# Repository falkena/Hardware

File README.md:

# Hardware
Some hardware extensions i developed for RaspberryPi.

Boards are made for rail - din enclosures.

Boards and schematics are published under Open Hardware License:
http://www.ohwr.org/licenses/cern-ohl/v1.2

DigitalIO
----------
MCP23017 based board supporting 8 digital inputs/outputs.
Inputs are opto-isolated and can be used up to 24V DC.
Outputs are relay driven. More details can be found in
documentation for used components.

Board can be driven for example with Pi4J.

AnalogI
-------
MCP3424 based board supporting 4 analog inputs.
Inputs are opto-isolated and can measure signals up to 10V DC.

Board can be driven for example with Pi4J.

Very special thanks to the guys from http://www.mikrocontroller.net

Automation board
----------------

Automation board for Raspberry PI. Designed to work with input voltage 15-24V.
Provides I2C connector, two wireless receiver for 433 and 868 MHZ as well PWM
fan 4 pin. Additional 2 pin connector can be used for shutdown with help of
`gpio-shutdown` overlay. Required 5V supply is done via MP1584 and MP2482 based
dc/dc step-down modules. See `modules` Eagle library for details.

Rain sensor
-----------

LM358 OpAmp based rain sensor detector. Designed to work with input voltage 15-24V.
Provides input and 10V digital outputs as well possibility to control heating.

Drop sensor is based on https://github.com/ranseyer/home-automatics/tree/master/Rain-Sensor/Kamm

Eagle
-------
Contains some cheap DIY boards i've used. Follow components are modeled now:
- RXB6 wireless receiver module
- RXB8 wireless receiver module
- CC1101 wireless transceiver/receiver module
- MP1584 based dc/dc step-down module
- MP2482 based dc/dc step-down module

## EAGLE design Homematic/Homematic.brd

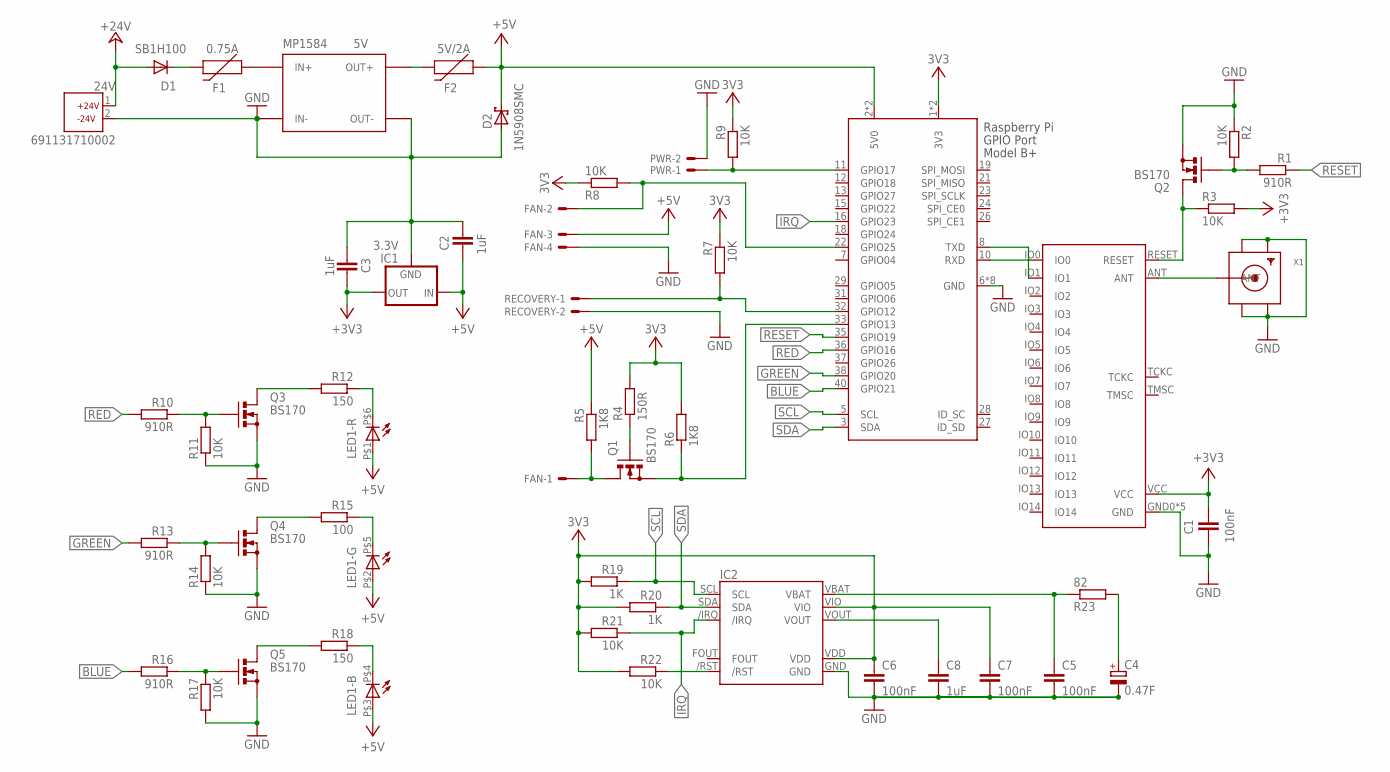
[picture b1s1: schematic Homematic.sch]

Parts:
24V: 691131710002
C1, C5, C6, C7: 100nF; C0805
C2, C3, C8: 1uF; C0805
C4: 0.47F; GOLDCAP-V
D1: SB1H100; DO41-7.6
D2: 1N5908SMC; SMC
F1: 0.75A; RGEF250
F2: 5V/2A; RGEF250
FAN: 22-23-2041
IC1: 3.3V; TO92
IC2: RX8130SMT; SMT-3225-10
LED1: LED-RGB; PLCC6
MP1584: 5V; MP1584V
PWR: 22-23-2021
Q1, Q2, Q3, Q4, Q5: BS170; SOT54E
R1: 910R; 0204/5
R2, R21, R22: 10K; 0204/5
R3, R7, R8, R9, R11, R14, R17: 10K; 0204V
R4: 150R; 0204V
R5, R6: 1K8; 0204V
R10, R13, R16: 910R; 0204V
R12, R18: 150; 0204V
R15: 100; 0204V
R19, R20: 1K; 0204/5
R23: 82; 0204/5
RECOVERY: 22-23-2021
RPI: RASPI_BOARD_B+#_F; RASPI_BOARD_B+_FULL
TRX2-TIF: TRXC2-TIFSMD; TRXC2-TIF
X1: SMACONNECTOR; SMA90_DIP

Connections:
3V3: C6.1, C7.1, IC2.VDD, IC2.VIO, R7.1, R8.1, R9.1, R19.2, R20.2, R21.2, R22.2, RPI.1 (3V3), RPI.17 (3V3)
+3V3: C1.1, C3.1, IC1.3 (OUT), R3.2, TRX2-TIF.VCC
+5V: C2.2, D2.C, F2.P$1 (1), FAN.3, IC1.2 (IN), LED1.P$1 (A), LED1.P$2 (A), LED1.P$3 (A), R5.1, RPI.2 (5V0), RPI.4 (5V0)
+24V: 24V.1, D1.A
BLUE: R16.2, RPI.40 (GPIO21)
GND: 24V.2, C1.2, C2.1, C3.2, C4.-, C5.2, C6.2, C7.2, C8.2, D2.A, FAN.4, IC1.1 (GND), IC2.GND, MP1584.IN-0 (IN-), MP1584.IN-1 (IN-), MP1584.OUT-0 (OUT-), MP1584.OUT-1 (OUT-), PWR.2, Q2.S, Q3.S, Q4.S, Q5.S, R2.1, R11.1, R14.1, R17.2, RECOVERY.2, RPI.6 (GND), RPI.9 (GND), RPI.14 (GND), RPI.20 (GND), RPI.25 (GND), RPI.30 (GND), RPI.34 (GND), RPI.39 (GND), TRX2-TIF.GND0 (GND), TRX2-TIF.GND1 (GND), TRX2-TIF.GND2 (GND), TRX2-TIF.GND3 (GND), TRX2-TIF.GND4 (GND), X1.GND1, X1.GND2, X1.GND3, X1.GND4
GREEN: R13.2, RPI.38 (GPIO20)
IRQ: IC2./IRQ, R21.1, RPI.16 (GPIO23)
unnamed: Q3.G, R10.1, R11.2
unnamed: RPI.10 (RXD), TRX2-TIF.IO0
unnamed: RPI.8 (TXD), TRX2-TIF.IO1
unnamed: F2.P$2 (2), MP1584.OUT+0 (OUT+), MP1584.OUT+1 (OUT+)
unnamed: Q4.G, R13.1, R14.2
unnamed: Q3.D, R12.2
unnamed: F1.P$1 (1), MP1584.IN+0 (IN+), MP1584.IN+1 (IN+)
unnamed: TRX2-TIF.ANT, X1.ANTENNA (ANT)
unnamed: D1.C, F1.P$2 (2)
unnamed: Q2.G, R1.2, R2.2
unnamed: Q1.G, R4.1
unnamed: Q5.G, R16.1, R17.1
unnamed: Q1.S, R6.1, RPI.33 (GPIO13)
unnamed: FAN.1, Q1.D, R5.2
unnamed: Q2.D, R3.1, TRX2-TIF.RESET
unnamed: Q4.D, R15.2
unnamed: Q5.D, R18.2
unnamed: LED1.P$6 (C), R12.1
unnamed: LED1.P$4 (C), R18.1
unnamed: LED1.P$5 (C), R15.1
unnamed: PWR.1, R9.2, RPI.11 (GPIO17)
unnamed: FAN.2, R8.2, RPI.22 (GPIO25)
unnamed: C4.+, R23.2
unnamed: C5.1, IC2.VBAT, R23.1
unnamed: IC2./RST, R22.1
unnamed: R7.2, RECOVERY.1, RPI.32 (GPIO12)
RED: R10.2, RPI.36 (GPIO16)
RESET: R1.1, RPI.35 (GPIO19)
SCL: IC2.SCL, R19.1, RPI.5 (SCL)
SDA: IC2.SDA, R20.1, RPI.3 (SDA)
V+: R4.2, R6.2
VOUT: C8.1, IC2.VOUT

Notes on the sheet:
+24V
-24V

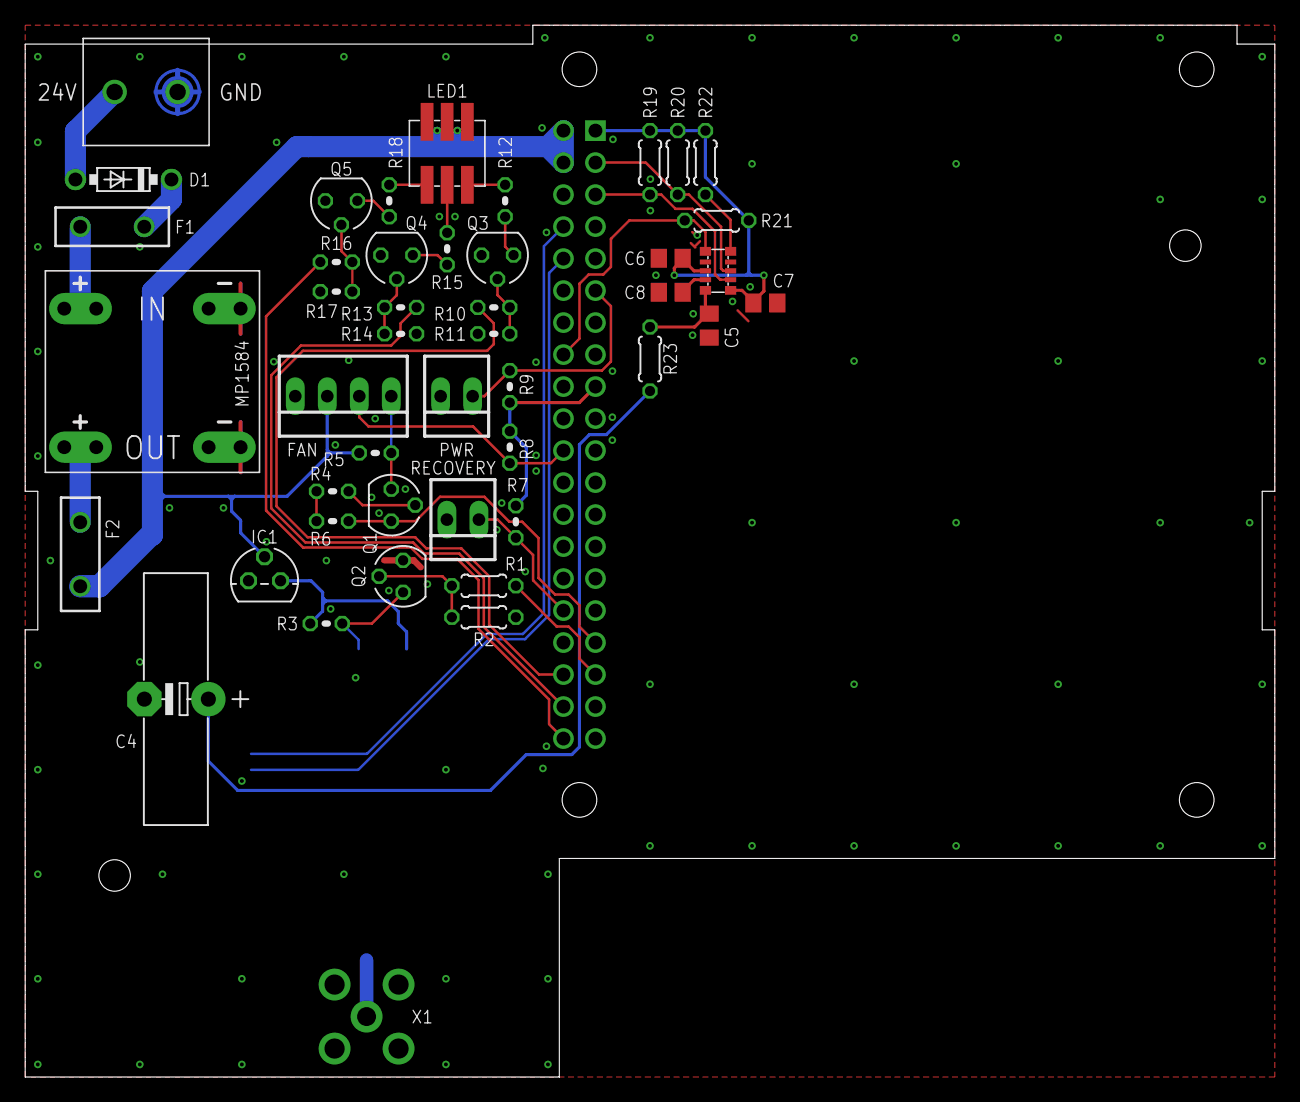
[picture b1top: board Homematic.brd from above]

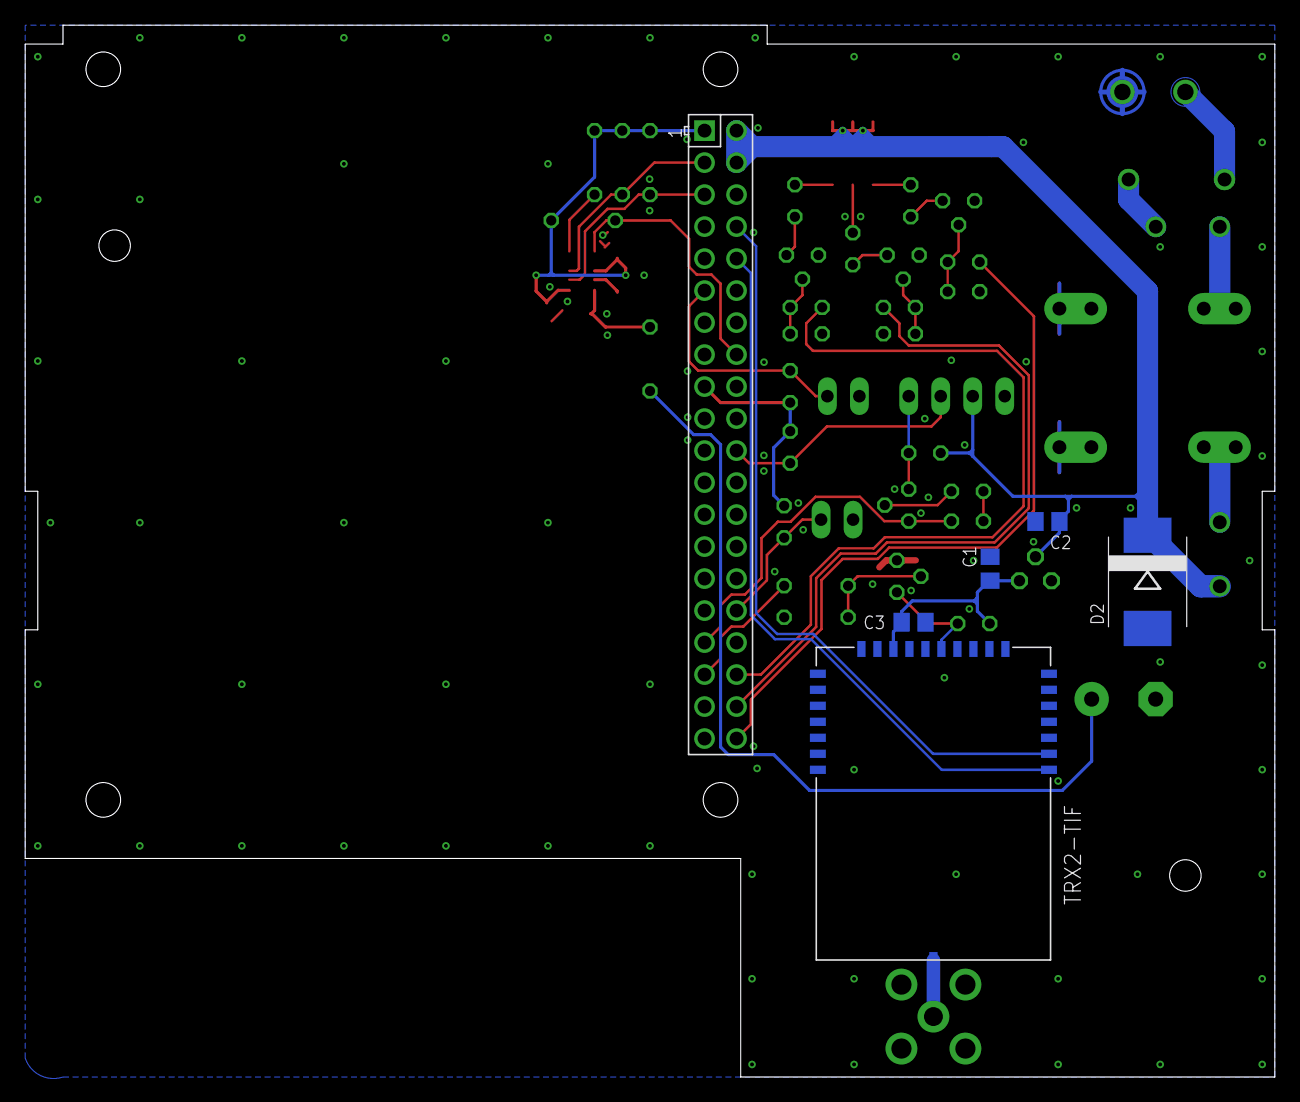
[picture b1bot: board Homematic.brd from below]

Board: 2 copper layers, 99.2 x 83.5 mm, 51 parts (6 on the bottom side), 40 nets.

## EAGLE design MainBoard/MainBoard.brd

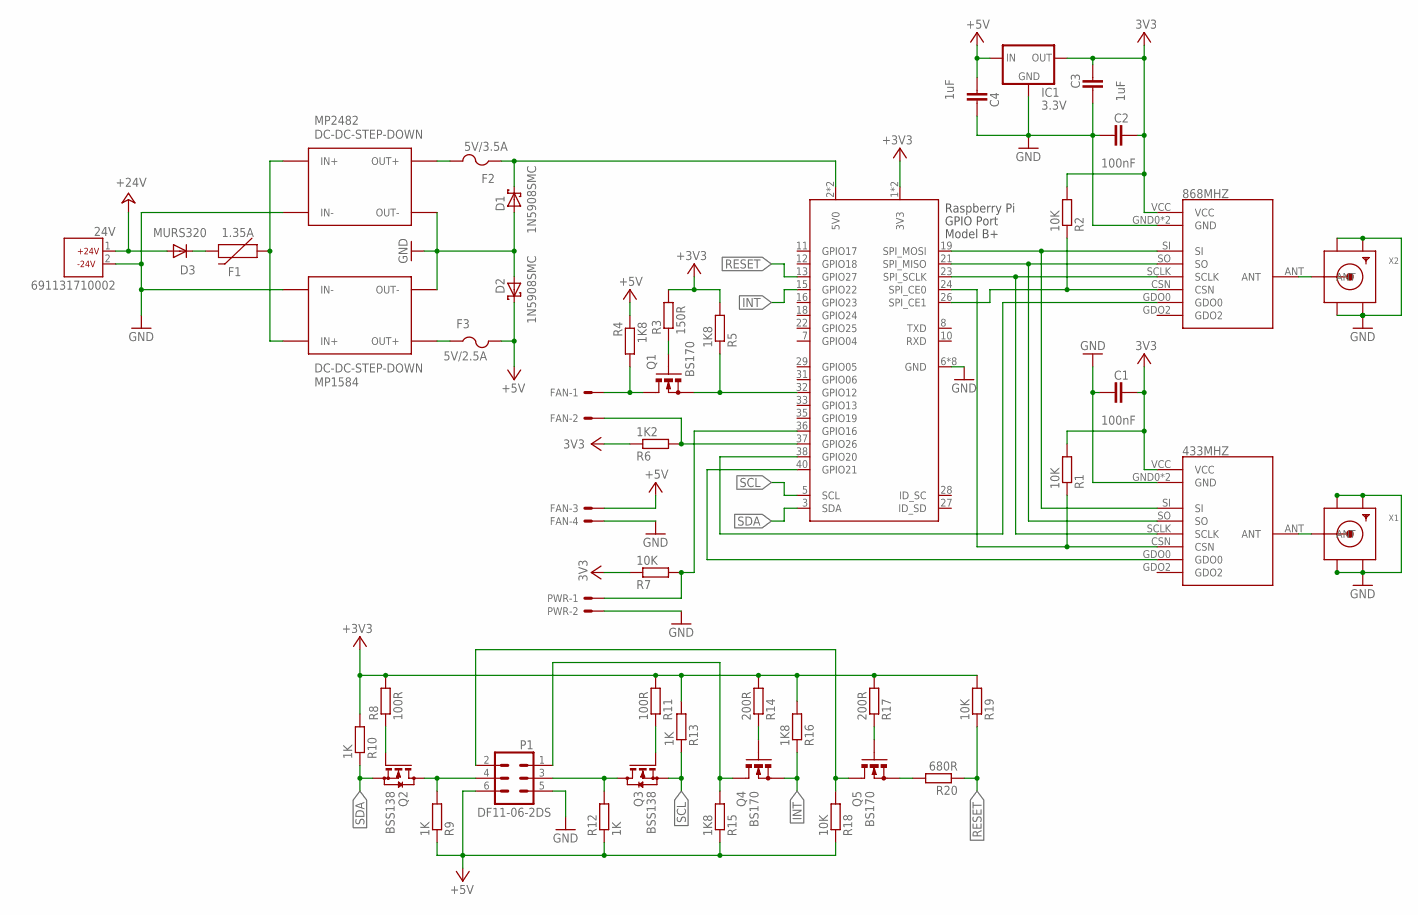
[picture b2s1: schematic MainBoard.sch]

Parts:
24V: 691131710002
433MHZ, 868MHZ: CC1101E07-SMD; E07-M1101S-SMD
C1, C2: 100nF; C0805
C3, C4: 1uF; C0805
D1, D2: 1N5908SMC; SMC
D3: MURS320; SMC
F1: 1.35A; RGEF250
F2: 5V/3.5A; 1812
F3: 5V/2.5A; 1812
FAN: 22-23-2041
IC1: 3.3V; TO92
MP1584: DC-DC-STEP-DOWN; MP1584V
MP2482: DC-DC-STEP-DOWN; MP2482V
P1: DF11-06-2DS; DF11-06DP-2DS
PWR: 22-23-2021
Q1, Q4, Q5: BS170; SOT54E
Q2, Q3: BSS138; SOT23
R1, R2, R7, R18, R19: 10K; 0204V
R3: 150R; 0204V
R4: 1K8; 0204/5
R5, R15, R16: 1K8; 0204V
R6: 1K2; 0204V
R8, R11: 100R; 0204/5
R9, R12: 1K; 0204V
R10, R13: 1K; 0204/5
R14, R17: 200R; 0204V
R20: 680R; 0204V
RPI: RASPI_BOARD_B+#_4F; RASPI_4_BOARD_B+_FULL
X1, X2: SMACONNECTOR; SMA90_DIP

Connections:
5V0: D1.C, F2.1, RPI.2 (5V0), RPI.4 (5V0)
+3V3: R3.2, R5.2, R6.1, R7.1, R8.2, R10.2, R11.2, R13.2, R14.2, R16.2, R17.2, R19.2, RPI.1 (3V3), RPI.17 (3V3)
+5V: C4.2, D2.C, F3.2, FAN.3, IC1.2 (IN), P1.6, R4.1, R9.1, R12.1, R15.1, R18.1
+24V: 24V.1, D3.A
GND: 24V.2, 433MHZ.GND0 (GND), 433MHZ.GND1 (GND), 868MHZ.GND0 (GND), 868MHZ.GND1 (GND), C1.2, C2.2, C3.2, C4.1, D1.A, D2.A, FAN.4, IC1.1 (GND), MP1584.IN-0 (IN-), MP1584.IN-1 (IN-), MP1584.OUT-0 (OUT-), MP1584.OUT-1 (OUT-), MP2482.IN-, MP2482.OUT-, P1.5, PWR.2, RPI.6 (GND), RPI.9 (GND), RPI.14 (GND), RPI.20 (GND), RPI.25 (GND), RPI.30 (GND), RPI.34 (GND), RPI.39 (GND), X1.GND1, X1.GND2, X1.GND3, X1.GND4, X2.GND1, X2.GND2, X2.GND3, X2.GND4
INT: Q4.S, R16.1, RPI.15 (GPIO22)
unnamed: P1.3, Q3.3 (D), R12.2
unnamed: Q1.G, R3.1
unnamed: 433MHZ.CSN, R1.1, RPI.24 (SPI_CE0)
unnamed: F2.2, MP2482.OUT+
unnamed: Q5.S, R20.2
unnamed: F3.1, MP1584.OUT+0 (OUT+), MP1584.OUT+1 (OUT+)
unnamed: F1.P$1 (1), MP1584.IN+0 (IN+), MP1584.IN+1 (IN+), MP2482.IN+
unnamed: 433MHZ.ANT, X1.ANTENNA (ANT)
unnamed: D3.C, F1.P$2 (2)
unnamed: 433MHZ.GDO0, RPI.40 (GPIO21)
unnamed: P1.4, Q2.3 (D), R9.2
unnamed: Q1.S, R5.1, RPI.32 (GPIO12)
unnamed: 868MHZ.CSN, R2.1, RPI.26 (SPI_CE1)
unnamed: 433MHZ.SCLK, 868MHZ.SCLK, RPI.23 (SPI_SCLK)
unnamed: 433MHZ.SO, 868MHZ.SO, RPI.21 (SPI_MISO)
unnamed: 433MHZ.SI, 868MHZ.SI, RPI.19 (SPI_MOSI)
unnamed: 868MHZ.GDO0, RPI.38 (GPIO20)
unnamed: 868MHZ.ANT, X2.ANTENNA (ANT)
unnamed: PWR.1, R7.2, RPI.36 (GPIO16)
unnamed: FAN.2, R6.2, RPI.37 (GPIO26)
unnamed: Q2.1 (G), R8.1
unnamed: Q3.1 (G), R11.1
unnamed: P1.1, Q4.D, R15.2
unnamed: P1.2, Q5.D, R18.2
unnamed: Q5.G, R17.1
unnamed: Q4.G, R14.1
unnamed: FAN.1, Q1.D, R4.2
RESET: R19.1, R20.1, RPI.13 (GPIO27)
SCL: Q3.2 (S), R13.1, RPI.5 (SCL)
SDA: Q2.2 (S), R10.1, RPI.3 (SDA)
VCC: 433MHZ.VCC, 868MHZ.VCC, C1.1, C2.1, C3.1, IC1.3 (OUT), R1.2, R2.2

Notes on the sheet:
+24V
-24V

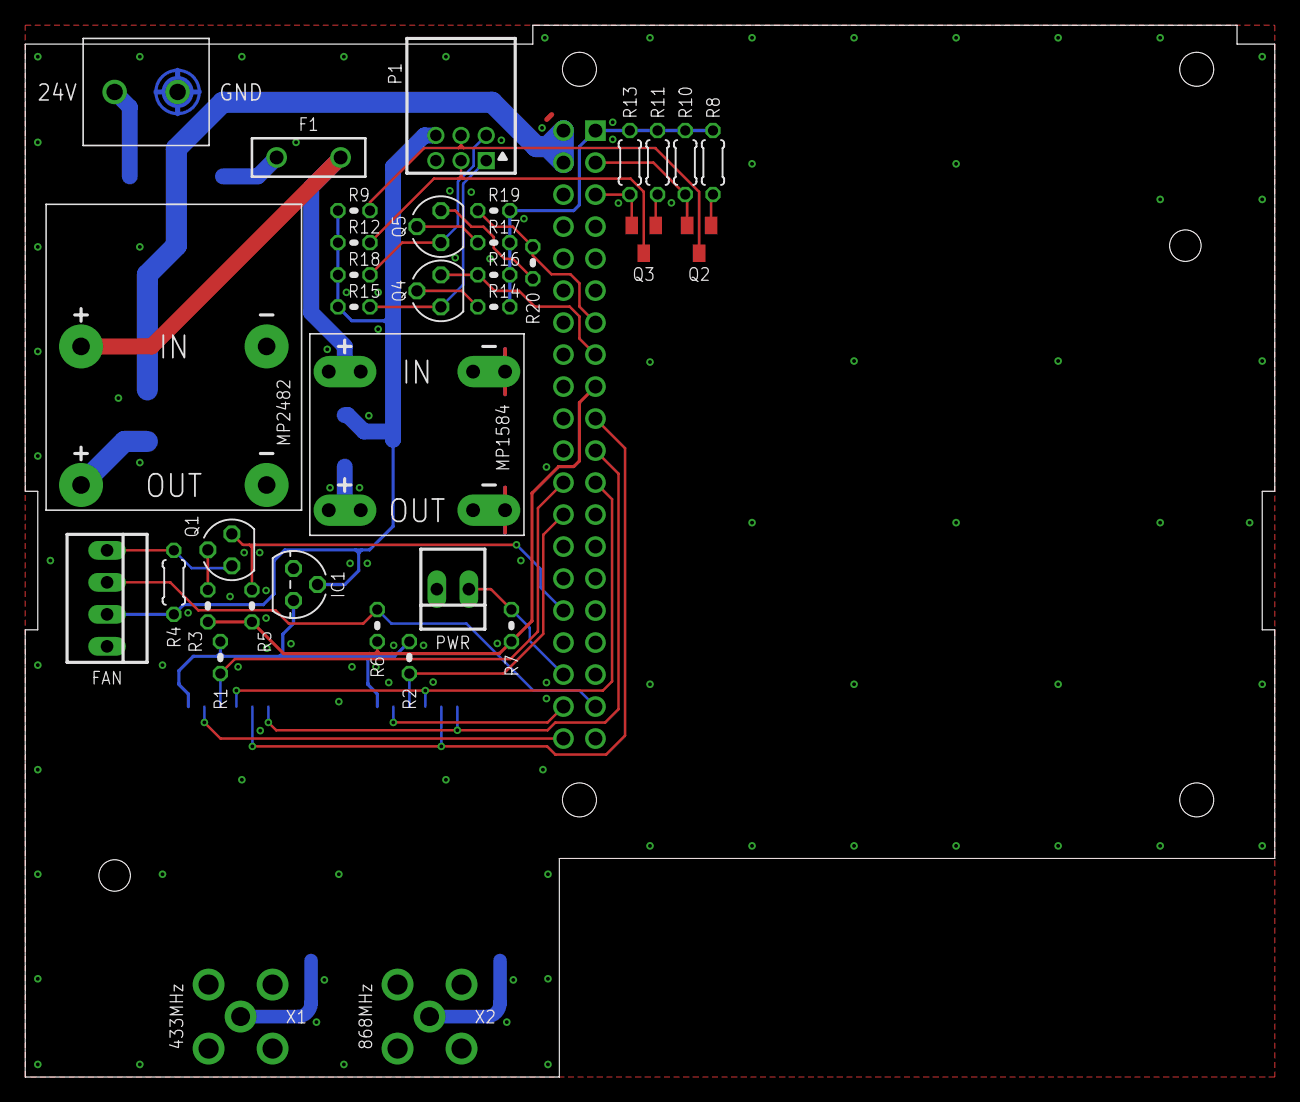
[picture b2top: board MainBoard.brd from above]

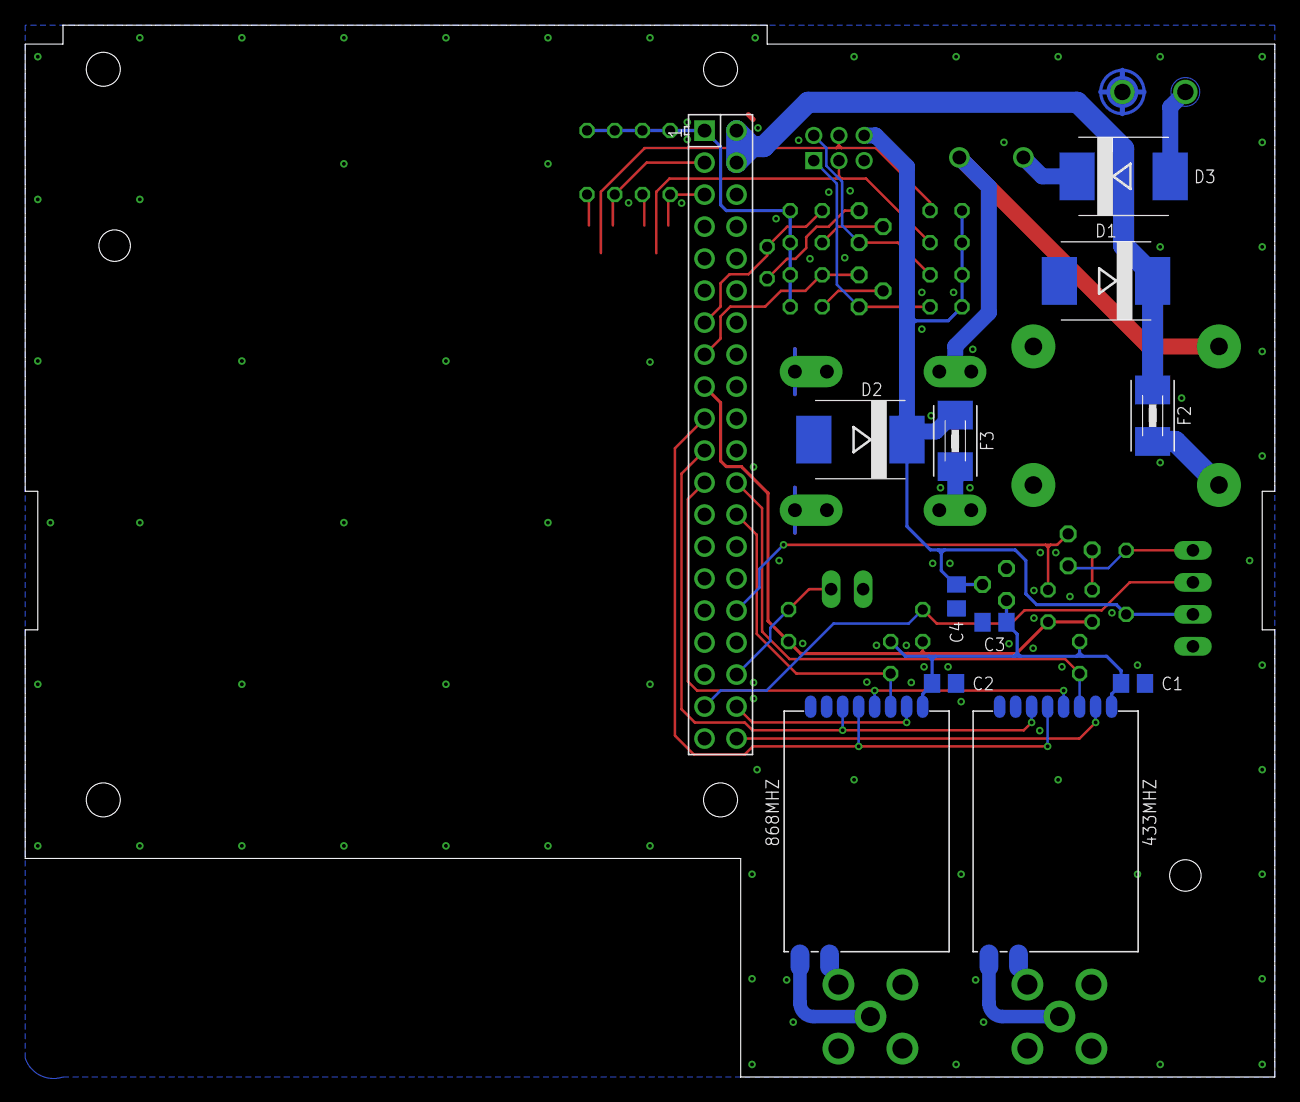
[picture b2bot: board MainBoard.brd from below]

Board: 2 copper layers, 99.2 x 83.5 mm, 47 parts (12 on the bottom side), 37 nets.

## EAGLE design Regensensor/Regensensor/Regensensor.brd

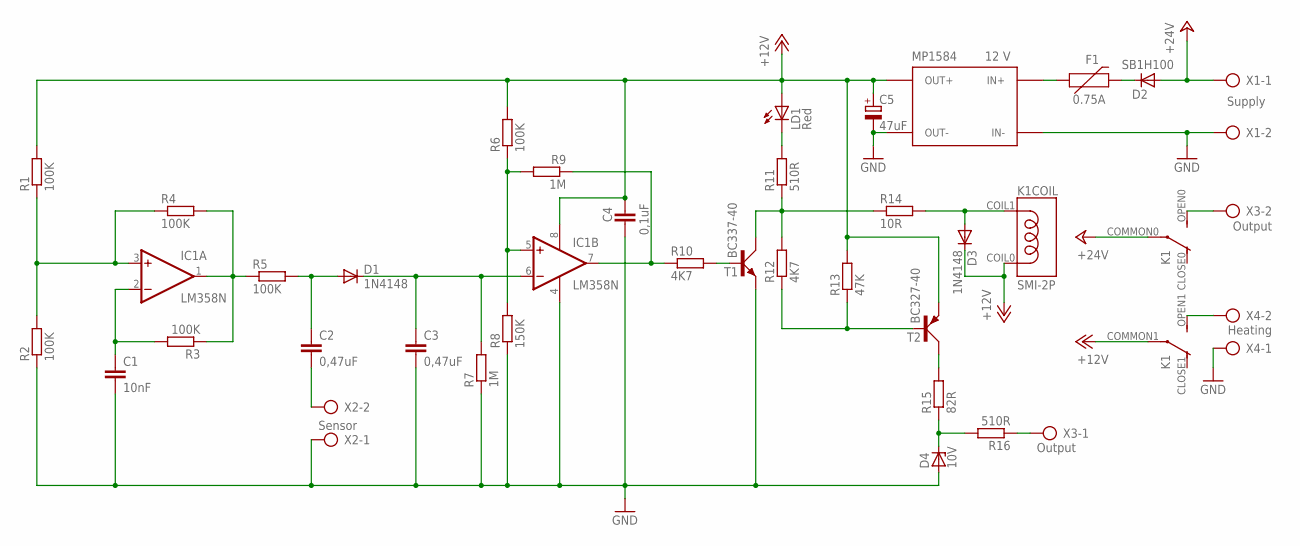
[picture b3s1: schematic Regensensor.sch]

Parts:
C1: 10nF; C050-055X075
C2, C3: 0,47uF; C050-035X075
C4: 0,1uF; C025-030X050
C5: 47uF; E5-6
D1: 1N4148; DO35-2V
D2: SB1H100; DO41-7.6
D3: 1N4148; DO35-7
D4: 10V; ZDIO-2.5
F1: 0.75A; RGEF250
IC1: LM358N; DIL08
K1: SMI-2P; SMI
LD1: Red; LED5MM
MP1584: 12 V; MP1584
R1, R2, R3, R5: 100K; 0204V
R4, R6: 100K; 0204/5
R7: 1M; 0204V
R8: 150K; 0204/5
R9: 1M; 0204/5
R10: 4K7; 0204/5
R11, R16: 510R; 0204V
R12: 4K7; 0204V
R13: 47K; 0204V
R14: 10R; 0204V
R15: 82R; 0204V
T1: BC337-40; TO92-LINE
T2: BC327-40; TO92-LINE
X1: Supply; MKDSB-3/2-2
X2: Sensor; MKDSB-3/2-2
X3: Output; MKDSB-3/2-2
X4: Heating; MKDSB-3/2-2

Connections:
+12V: C4.1, C5.+, D3.C, IC1.8 (V+), K1.COIL0 (0), K1.COMMON1 (COMMON), LD1.A, MP1584.OUT+0 (OUT+), MP1584.OUT+1 (OUT+), R1.2, R6.2, R13.2, T2.1 (E)
+24V: D2.A, K1.COMMON0 (COMMON), X1.1
GND: C1.2, C3.2, C4.2, C5.-, D4.A, IC1.4 (V-), MP1584.IN-0 (IN-), MP1584.IN-1 (IN-), MP1584.OUT-0 (OUT-), MP1584.OUT-1 (OUT-), R2.1, R7.1, R8.1, T1.1 (E), X1.2, X2.1, X4.1
unnamed: IC1.5 (+IN), R6.1, R8.2, R9.2
unnamed: IC1.7 (OUT), R9.1, R10.1
unnamed: C3.1, D1.C, IC1.6 (-IN), R7.2
unnamed: C2.1, D1.A, R5.2
unnamed: R10.2, T1.2 (B)
unnamed: C1.1, IC1.2 (-IN), R3.2
unnamed: IC1.1 (OUT), R3.1, R4.2, R5.1
unnamed: F1.P$1 (1), MP1584.IN+0 (IN+), MP1584.IN+1 (IN+)
unnamed: IC1.3 (+IN), R1.1, R2.2, R4.1
unnamed: R11.1, R12.2, R14.1, T1.3 (C)
unnamed: R12.1, R13.1, T2.2 (B)
unnamed: LD1.K (C), R11.2
unnamed: C2.2, X2.2
unnamed: D3.A, K1.COIL1 (1), R14.2
unnamed: D4.C, R15.1, R16.2
unnamed: K1.OPEN0 (OPEN), X3.2
unnamed: K1.OPEN1 (OPEN), X4.2
unnamed: D2.C, F1.P$2 (2)
unnamed: R15.2, T2.3 (C)
unnamed: R16.1, X3.1

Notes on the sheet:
Output

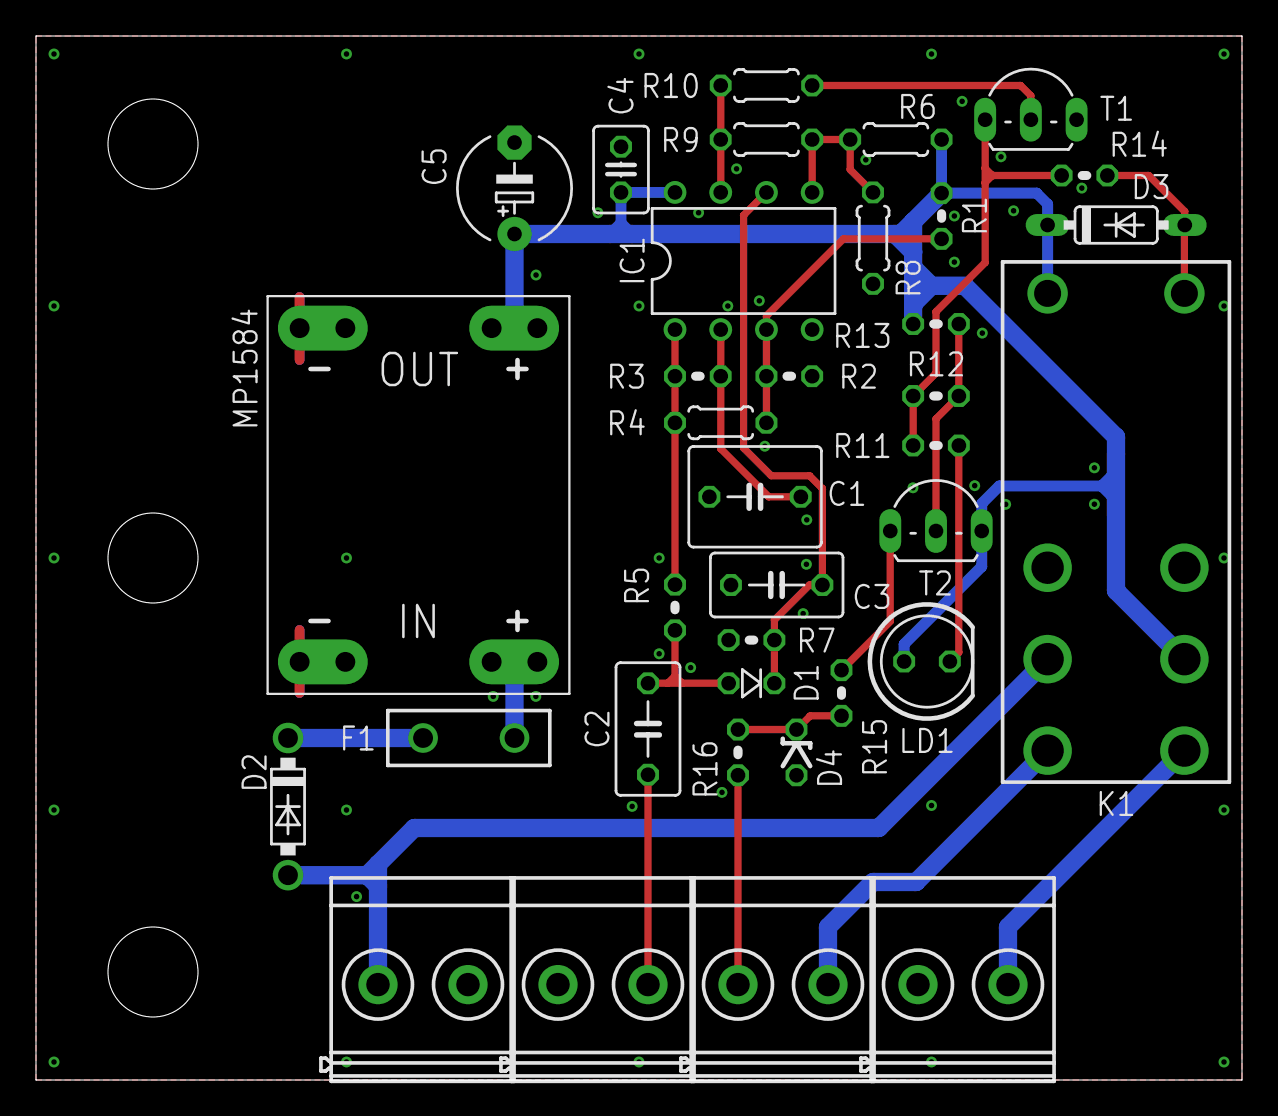
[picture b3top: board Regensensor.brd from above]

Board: 2 copper layers, 67.0 x 58.0 mm, 36 parts (0 on the bottom side), 23 nets.

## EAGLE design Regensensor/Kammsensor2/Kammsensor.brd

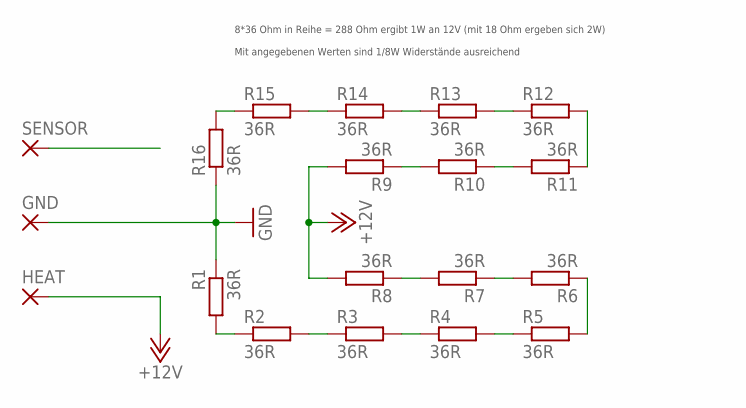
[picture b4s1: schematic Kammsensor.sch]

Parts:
GND: WIREPADSMD5-1,8; 5-1,8
HEAT: WIREPADSMD5-1,8; 5-1,8
R1, R2, R3, R4, R5, R6, R7, R8, R9, R10, R11, R12, R13, R14, R15, R16: 36R; M1206
SENSOR: WIREPADSMD5-1,8; 5-1,8

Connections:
+12V: HEAT.1, R8.2, R9.2
GND: GND.1, R1.1, R16.1
unnamed: R3.2, R4.1
unnamed: R2.2, R3.1
unnamed: R14.1, R15.2
unnamed: R4.2, R5.1
unnamed: R5.2, R6.1
unnamed: R6.2, R7.1
unnamed: R1.2, R2.1
unnamed: R7.2, R8.1
unnamed: R9.1, R10.2
unnamed: R10.1, R11.2
unnamed: R11.1, R12.2
unnamed: R12.1, R13.2
unnamed: R13.1, R14.2
unnamed: R15.1, R16.2
SENSOR: SENSOR.1

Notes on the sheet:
8*36 Ohm in Reihe = 288 Ohm ergibt 1W an 12V (mit 18 Ohm ergeben sich 2W) Mit angegebenen Werten sind 1/8W Widerstände ausreichend

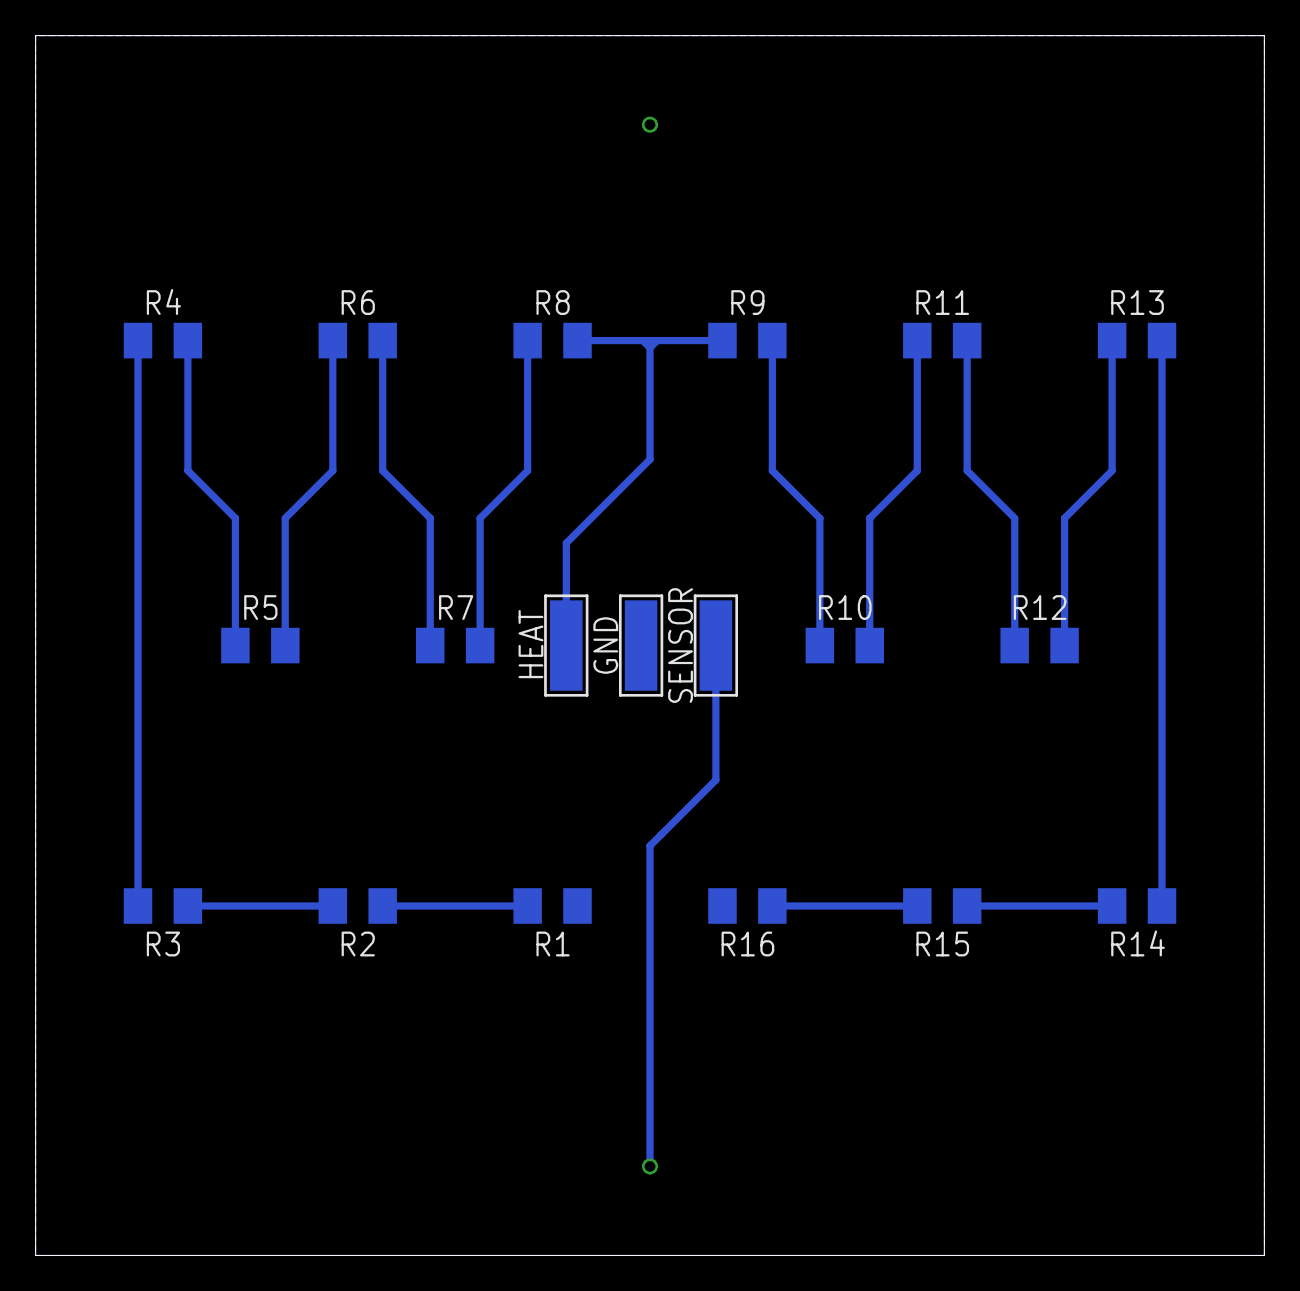
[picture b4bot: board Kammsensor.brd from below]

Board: 2 copper layers, 69.0 x 68.5 mm, 19 parts (19 on the bottom side), 16 nets.

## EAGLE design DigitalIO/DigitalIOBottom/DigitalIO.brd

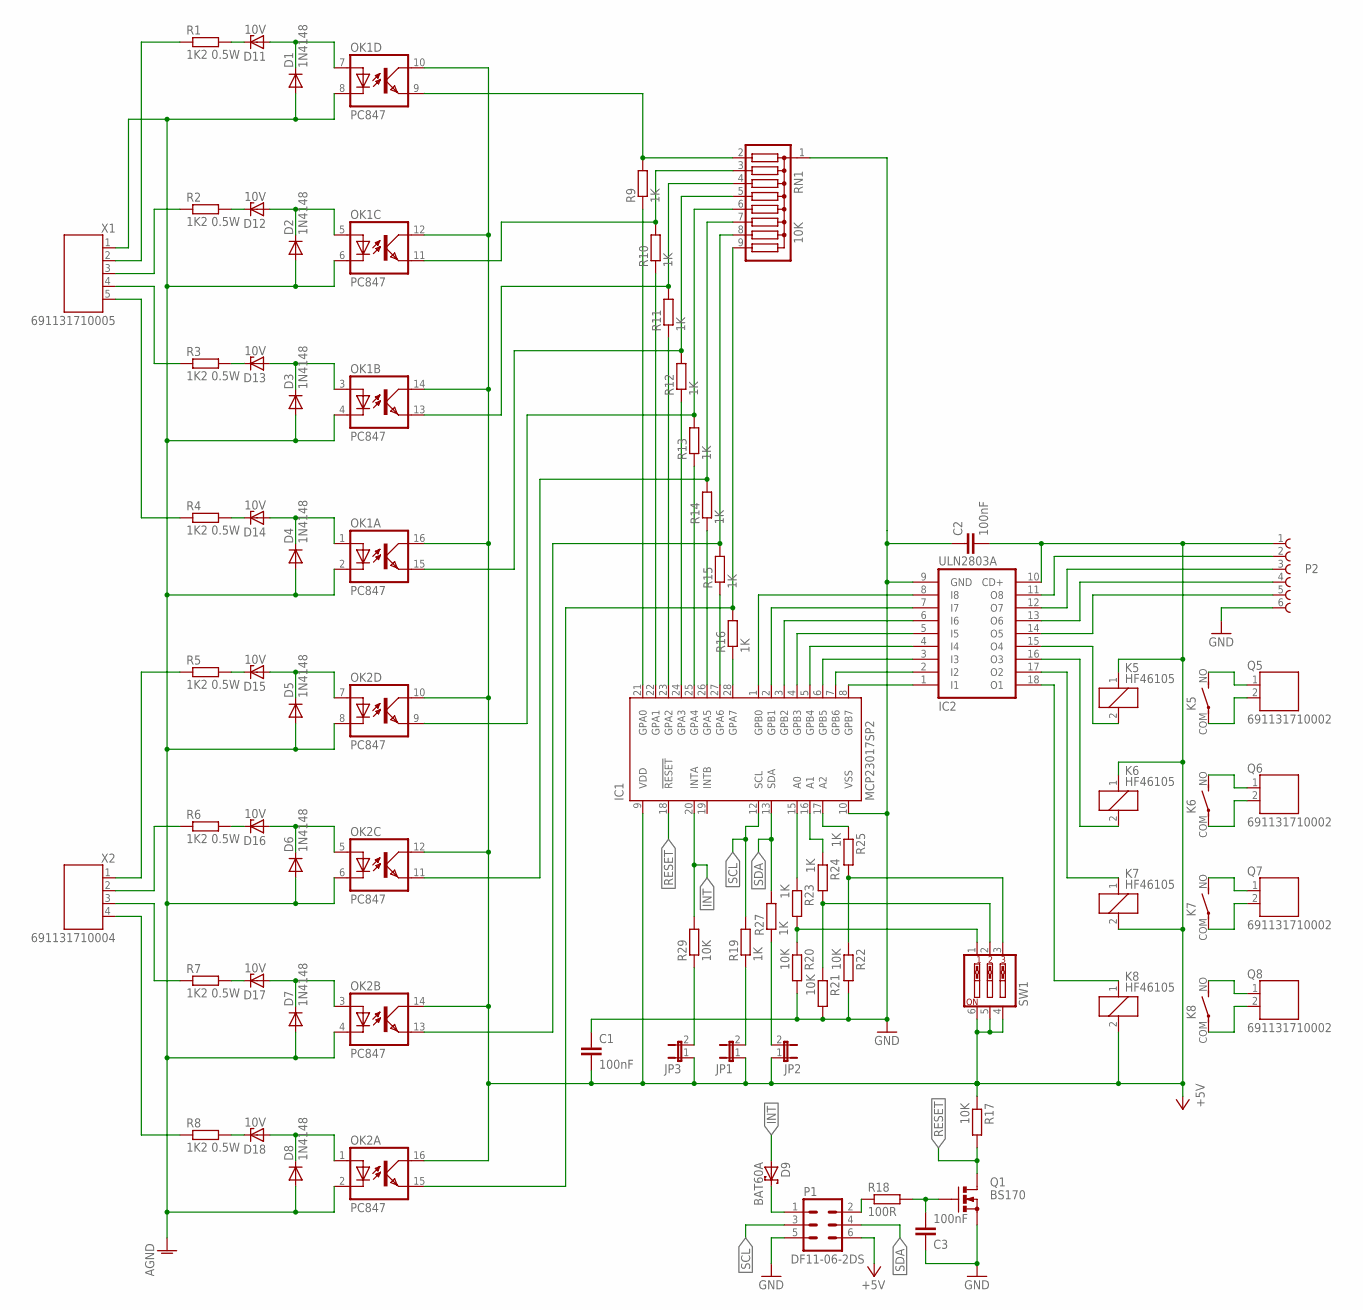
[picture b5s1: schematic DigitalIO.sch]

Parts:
C1, C2, C3: 100nF; C0805; MPN MCRR50104X7RK0050
D1, D2, D3, D4, D5, D6, D7, D8: 1N4148; DO35-2V
D9: BAT60A; SOD323_ST
D11, D12, D13, D14, D15, D16, D17, D18: 10V; ZDIO-2.5
IC1: MCP23017SP2; DIL28-3-ROUND
IC2: ULN2803A; DIL18-ROUND; MPN ULN2803A
JP1, JP2, JP3: JP1E; JP1
K5, K6, K7, K8: HF46105; HF46
OK1, OK2: PC847; DIL16
P1: DF11-06-2DS; DF11-06DP-2DS
P2: 62000611121
Q1: BS170; SOT54E
Q5, Q6, Q7, Q8: 691131710002
R1, R2, R3, R4, R5, R6, R7, R8: 1K2 0.5W; 0207/2V; MPN MCF 0.25W 1K2
R9, R10, R11, R12, R13, R14, R15, R16, R19, R23, R24, R25, R27: 1K; 0204V
R17, R20, R21, R22, R29: 10K; 0204V
R18: 100R; 0204V
RN1: 10K; SIL9
SW1: SW_DIP-3; EDG-03
X1: 691131710005
X2: 691131710004

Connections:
+5V: C1.2, C2.2, IC1.9 (VDD), IC2.10 (CD+), JP1.1, JP2.1, JP3.1, K5.1, K6.1, K7.2, K8.2, OK1.10 (COL), OK1.12 (COL), OK1.14 (COL), OK1.16 (COL), OK2.10 (COL), OK2.12 (COL), OK2.14 (COL), OK2.16 (COL), P1.6, P2.1, R17.1, SW1.4, SW1.5, SW1.6
AGND: D1.A, D2.A, D3.A, D4.A, D5.A, D6.A, D7.A, D8.A, OK1.2 (C), OK1.4 (C), OK1.6 (C), OK1.8 (C), OK2.2 (C), OK2.4 (C), OK2.6 (C), OK2.8 (C), X1.1
GND: C1.1, C2.1, C3.1, IC1.10 (VSS), IC2.9 (GND), P1.5, P2.6, Q1.S, R20.2, R21.2, R22.2, RN1.1
INT: D9.A, IC1.20 (INTA), R29.2
unnamed: IC1.8 (GPB7), IC2.1 (I1)
unnamed: IC1.7 (GPB6), IC2.2 (I2)
unnamed: IC1.6 (GPB5), IC2.3 (I3)
unnamed: IC1.5 (GPB4), IC2.4 (I4)
unnamed: IC1.4 (GPB3), IC2.5 (I5)
unnamed: IC1.3 (GPB2), IC2.6 (I6)
unnamed: IC1.2 (GPB1), IC2.7 (I7)
unnamed: IC1.1 (GPB0), IC2.8 (I8)
unnamed: D12.C, R2.2
unnamed: D11.C, R1.2
unnamed: R22.1, R25.2, SW1.3
unnamed: D1.C, D11.A, OK1.7 (A)
unnamed: R6.1, X2.2
unnamed: R2.1, X1.3
unnamed: OK1.9 (EMIT), R9.2, RN1.2
unnamed: R3.1, X1.4
unnamed: R7.1, X2.3
unnamed: R1.1, X1.2
unnamed: D2.C, D12.A, OK1.5 (A)
unnamed: OK1.11 (EMIT), R10.2, RN1.3
unnamed: D13.C, R3.2
unnamed: R4.1, X1.5
unnamed: D3.C, D13.A, OK1.3 (A)
unnamed: R5.1, X2.1
unnamed: OK1.13 (EMIT), R11.2, RN1.4
unnamed: R8.1, X2.4
unnamed: D14.C, R4.2
unnamed: IC2.14 (O5), P2.5
unnamed: D4.C, D14.A, OK1.1 (A)
unnamed: IC2.13 (O6), P2.4
unnamed: OK1.15 (EMIT), R12.2, RN1.5
unnamed: IC2.12 (O7), P2.3
unnamed: D15.C, R5.2
unnamed: IC2.11 (O8), P2.2
unnamed: D5.C, D15.A, OK2.7 (A)
unnamed: JP2.2, R27.1
unnamed: OK2.9 (EMIT), R13.2, RN1.6
unnamed: K8.NO (S), Q8.1
unnamed: D16.C, R6.2
unnamed: K8.COM, Q8.2
unnamed: D6.C, D16.A, OK2.5 (A)
unnamed: IC2.15 (O4), K5.2
unnamed: OK2.11 (EMIT), R14.2, RN1.7
unnamed: K7.NO (S), Q7.1
unnamed: D17.C, R7.2
unnamed: K7.COM, Q7.2
unnamed: D7.C, D17.A, OK2.3 (A)
unnamed: IC2.16 (O3), K6.2
unnamed: OK2.13 (EMIT), R15.2, RN1.8
unnamed: IC1.15 (A0), R23.1
unnamed: D18.C, R8.2
unnamed: IC1.16 (A1), R24.1
unnamed: D8.C, D18.A, OK2.1 (A)
unnamed: IC2.17 (O2), K7.1
unnamed: OK2.15 (EMIT), R16.2, RN1.9
unnamed: IC2.18 (O1), K8.1
unnamed: JP3.2, R29.1
unnamed: IC1.21 (GPA0), R9.1
unnamed: IC1.22 (GPA1), R10.1
unnamed: JP1.2, R19.1
unnamed: IC1.23 (GPA2), R11.1
unnamed: IC1.28 (GPA7), R16.1
unnamed: IC1.27 (GPA6), R15.1
unnamed: IC1.26 (GPA5), R14.1
unnamed: K5.NO (S), Q5.1
unnamed: IC1.25 (GPA4), R13.1
unnamed: IC1.24 (GPA3), R12.1
unnamed: P1.2, R18.1
unnamed: C3.2, Q1.G, R18.2
unnamed: K5.COM, Q5.2
unnamed: R20.1, R23.2, SW1.1
unnamed: R21.1, R24.2, SW1.2
unnamed: IC1.17 (A2), R25.1
unnamed: D9.C, P1.1
unnamed: K6.NO (S), Q6.1
unnamed: K6.COM, Q6.2
RESET: IC1.18 (!RESET), Q1.D, R17.2
SCL: IC1.12 (SCL), P1.3, R19.2
SDA: IC1.13 (SDA), P1.4, R27.2

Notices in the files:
parts and their libraries:
con-wuerth: Copyright: Würth Elektronik
SparkFun-AnalogIC: Licensing:Creative Commons ShareAlike 4.0 International - https://creativecommons.org/licenses/by-sa/4.0
con-jst-ph: Copyright (C) 2016, Bob Starr
modules: Released under the Open Hardware License: http://www.ohwr.org/licenses/cern-ohl/v1.2
